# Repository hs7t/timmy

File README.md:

# Timmy

Timmy is a small [hackpad](https://hackpad.hackclub.com/) input device!
It features:

- a custom PCB
- two fun knobs
- 9 keys
- a pretty cool case!

## Parts

Timmy is composed of a case and two knob caps, totaling four
3D-printed pieces (the case top and bottom, a round knob, and a square knob).
It took me a bit to arrive at this design, and I'm quite fond of
it! Everything fits together using heatset inserts for 4 M3 bolts.

## PCB

The PCB was designed in KiCAD. It's my first PCB ever, so it might
not be that great!

This board is double-layered and has a ground copper fill.

## Materials

- 1 Seeed XIAO RP2040
- 9 through-hole 1N4148 Diodes
- 9 MX-Style switches
- 2 EC11 Rotary encoders
- 9 DSA keycaps
- 16 SK6812 MINI-E LEDs
- 4 M3x16mm screws
- 4 M3x5mx4mm heatset inserts
- 4 3D printed parts
- 1 double-layered PCB

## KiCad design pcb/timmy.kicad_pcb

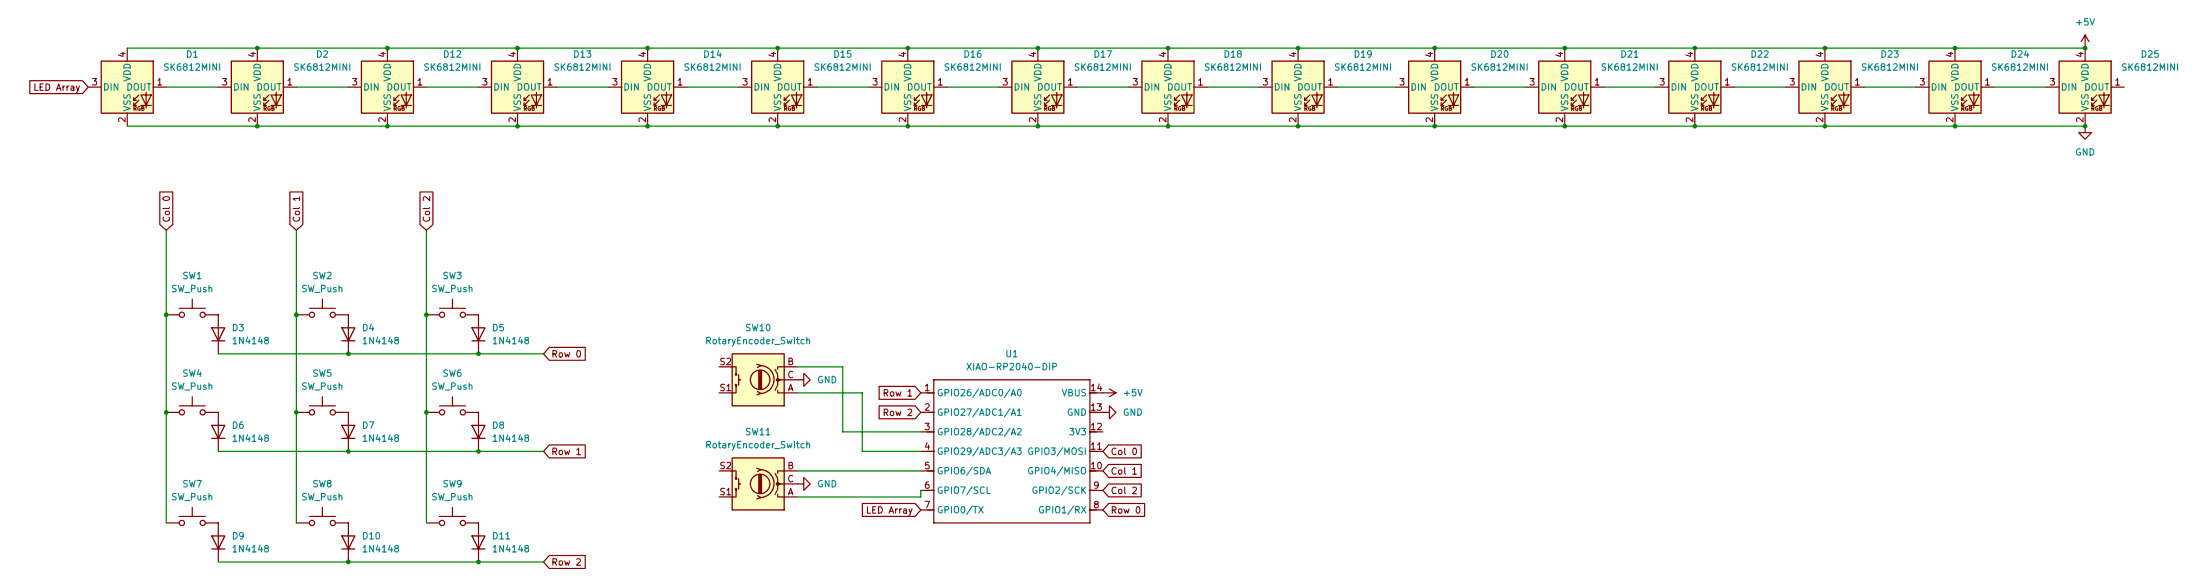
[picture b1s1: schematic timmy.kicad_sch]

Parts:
D1, D2, D12, D13, D14, D15, D16, D17, D18, D19, D20, D21, D22, D23, D24, D25: SK6812MINI; sk6812-mini-e
D3, D4, D5, D6, D7, D8, D9, D10, D11: 1N4148; D_DO-35_SOD27_P7.62mm_Horizontal
SW1, SW2, SW3, SW4, SW5, SW6, SW7, SW8, SW9: SW_Push; SW_Cherry_MX_1.00u_PCB
SW10, SW11: RotaryEncoder_Switch; RotaryEncoder_Alps_EC11E-Switch_Vertical_H20mm
U1: XIAO-RP2040-DIP

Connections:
+5V: D1.4 (VDD), D2.4 (VDD), D12.4 (VDD), D13.4 (VDD), D14.4 (VDD), D15.4 (VDD), D16.4 (VDD), D17.4 (VDD), D18.4 (VDD), D19.4 (VDD), D20.4 (VDD), D21.4 (VDD), D22.4 (VDD), D23.4 (VDD), D24.4 (VDD), D25.4 (VDD), U1.14 (VBUS)
Col 0: SW1.1, SW4.1, SW7.1, U1.11 (GPIO3/MOSI)
Col 1: SW2.1, SW5.1, SW8.1, U1.10 (GPIO4/MISO)
Col 2: SW3.1, SW6.1, SW9.1, U1.9 (GPIO2/SCK)
GND: D1.2 (VSS), D2.2 (VSS), D12.2 (VSS), D13.2 (VSS), D14.2 (VSS), D15.2 (VSS), D16.2 (VSS), D17.2 (VSS), D18.2 (VSS), D19.2 (VSS), D20.2 (VSS), D21.2 (VSS), D22.2 (VSS), D23.2 (VSS), D24.2 (VSS), D25.2 (VSS), SW10.C, SW11.C, U1.13 (GND)
LED Array: D1.3 (DIN), U1.7 (GPIO0/TX)
unnamed: D1.1 (DOUT), D2.3 (DIN)
unnamed: D3.2 (A), SW1.2
unnamed: D4.2 (A), SW2.2
unnamed: D5.2 (A), SW3.2
unnamed: D6.2 (A), SW4.2
unnamed: D7.2 (A), SW5.2
unnamed: D8.2 (A), SW6.2
unnamed: D9.2 (A), SW7.2
unnamed: D10.2 (A), SW8.2
unnamed: D11.2 (A), SW9.2
unnamed: D2.1 (DOUT), D12.3 (DIN)
unnamed: D12.1 (DOUT), D13.3 (DIN)
unnamed: D13.1 (DOUT), D14.3 (DIN)
unnamed: D14.1 (DOUT), D15.3 (DIN)
unnamed: D15.1 (DOUT), D16.3 (DIN)
unnamed: D16.1 (DOUT), D17.3 (DIN)
unnamed: D17.1 (DOUT), D18.3 (DIN)
unnamed: D18.1 (DOUT), D19.3 (DIN)
unnamed: D19.1 (DOUT), D20.3 (DIN)
unnamed: D20.1 (DOUT), D21.3 (DIN)
unnamed: D21.1 (DOUT), D22.3 (DIN)
unnamed: D22.1 (DOUT), D23.3 (DIN)
unnamed: D23.1 (DOUT), D24.3 (DIN)
unnamed: D24.1 (DOUT), D25.3 (DIN)
unnamed: SW11.B, U1.5 (GPIO6/SDA)
unnamed: SW11.A, U1.6 (GPIO7/SCL)
unnamed: SW10.B, U1.3 (GPIO28/ADC2/A2)
unnamed: SW10.A, U1.4 (GPIO29/ADC3/A3)
Row 0: D3.1 (K), D4.1 (K), D5.1 (K), U1.8 (GPIO1/RX)
Row 1: D6.1 (K), D7.1 (K), D8.1 (K), U1.1 (GPIO26/ADC0/A0)
Row 2: D9.1 (K), D10.1 (K), D11.1 (K), U1.2 (GPIO27/ADC1/A1)

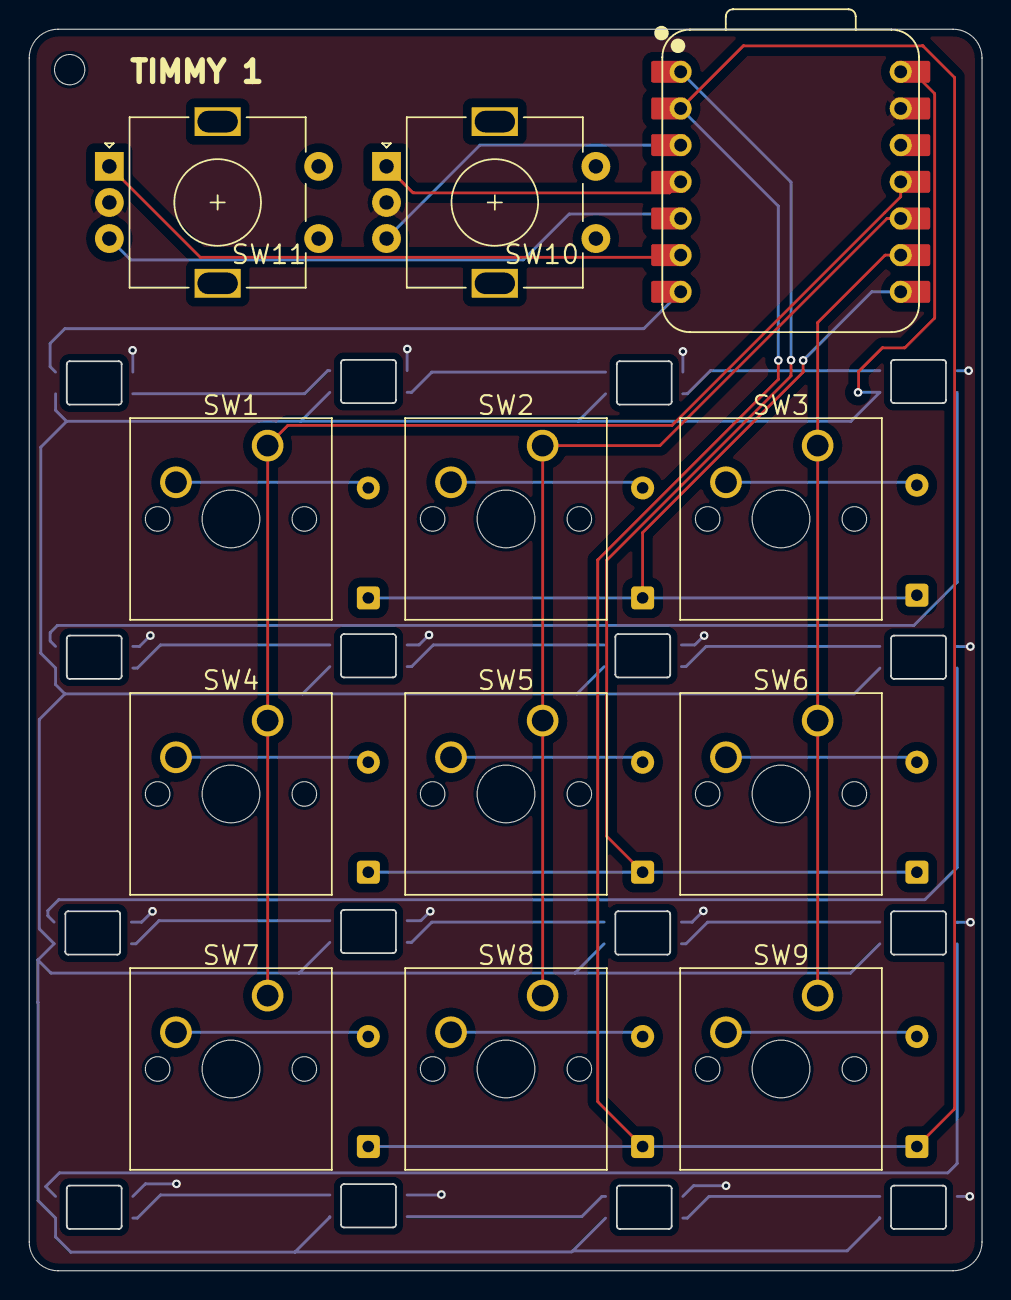
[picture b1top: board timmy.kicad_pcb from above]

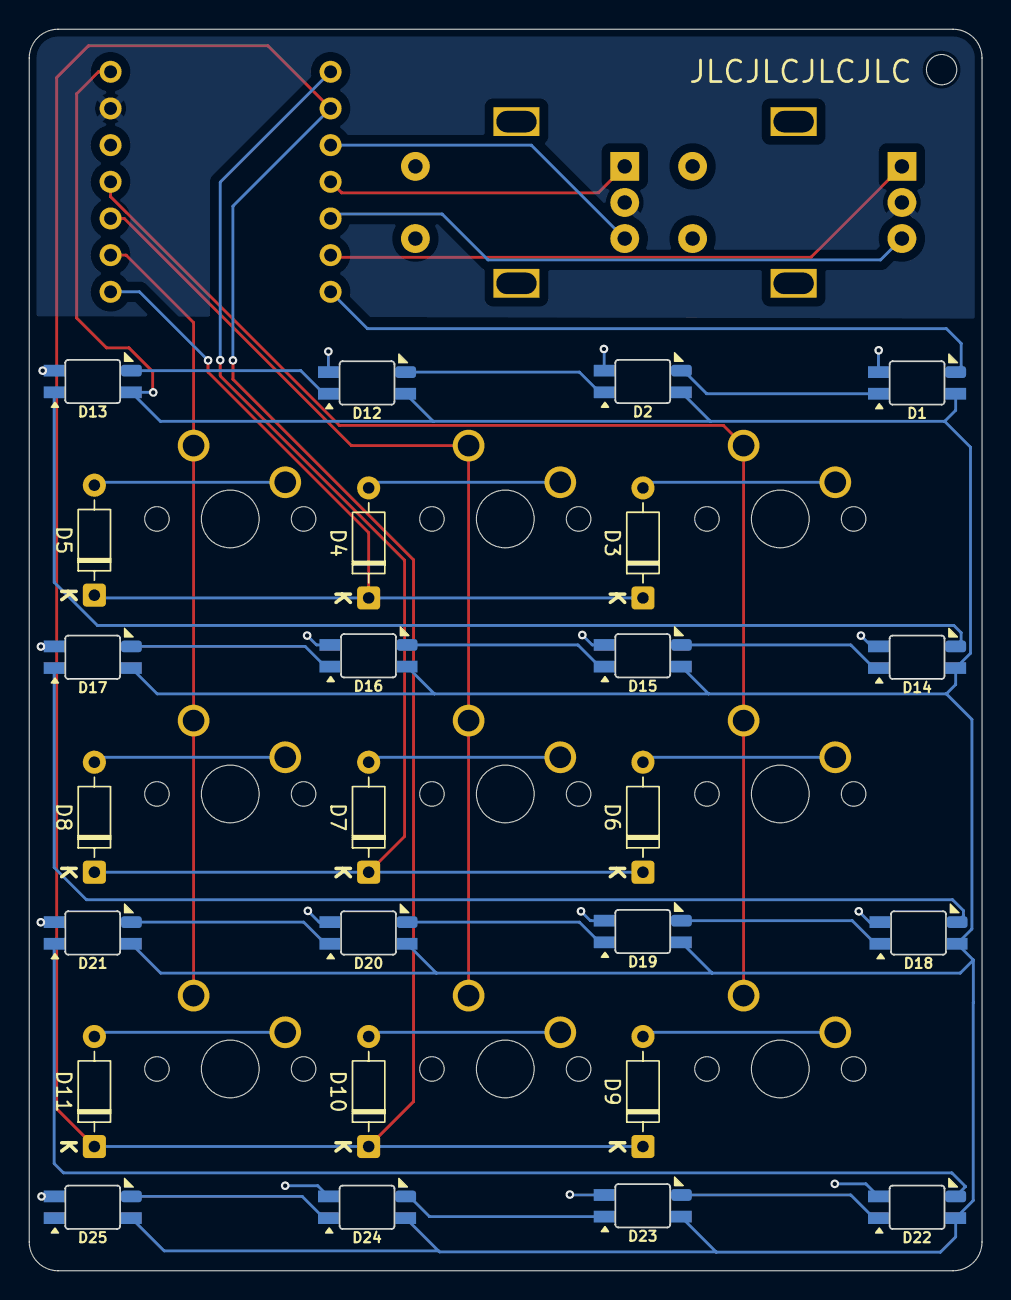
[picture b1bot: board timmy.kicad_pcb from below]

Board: 4 copper layers, 65.9 x 85.9 mm, 37 parts (25 on the bottom side), 37 nets.

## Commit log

2025-07-19 upload project files!
2025-07-23 update to accomodate back-mounted LEDs
